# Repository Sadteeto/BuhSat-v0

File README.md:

BUH SAT so that we have an MVP for AURC! <br />
git clone this repo and import to platformIO. <br />
compiled uf2 file can be found in Actions tab - Artifacts <br />

capabilities: <br />
battery charging <br />
remote monitoring up to 40km <br />
temperature monitoring<br />
9-DOF motion monitoring <br />
 - gyro <br />
 - accel <br />
 - mag <br />

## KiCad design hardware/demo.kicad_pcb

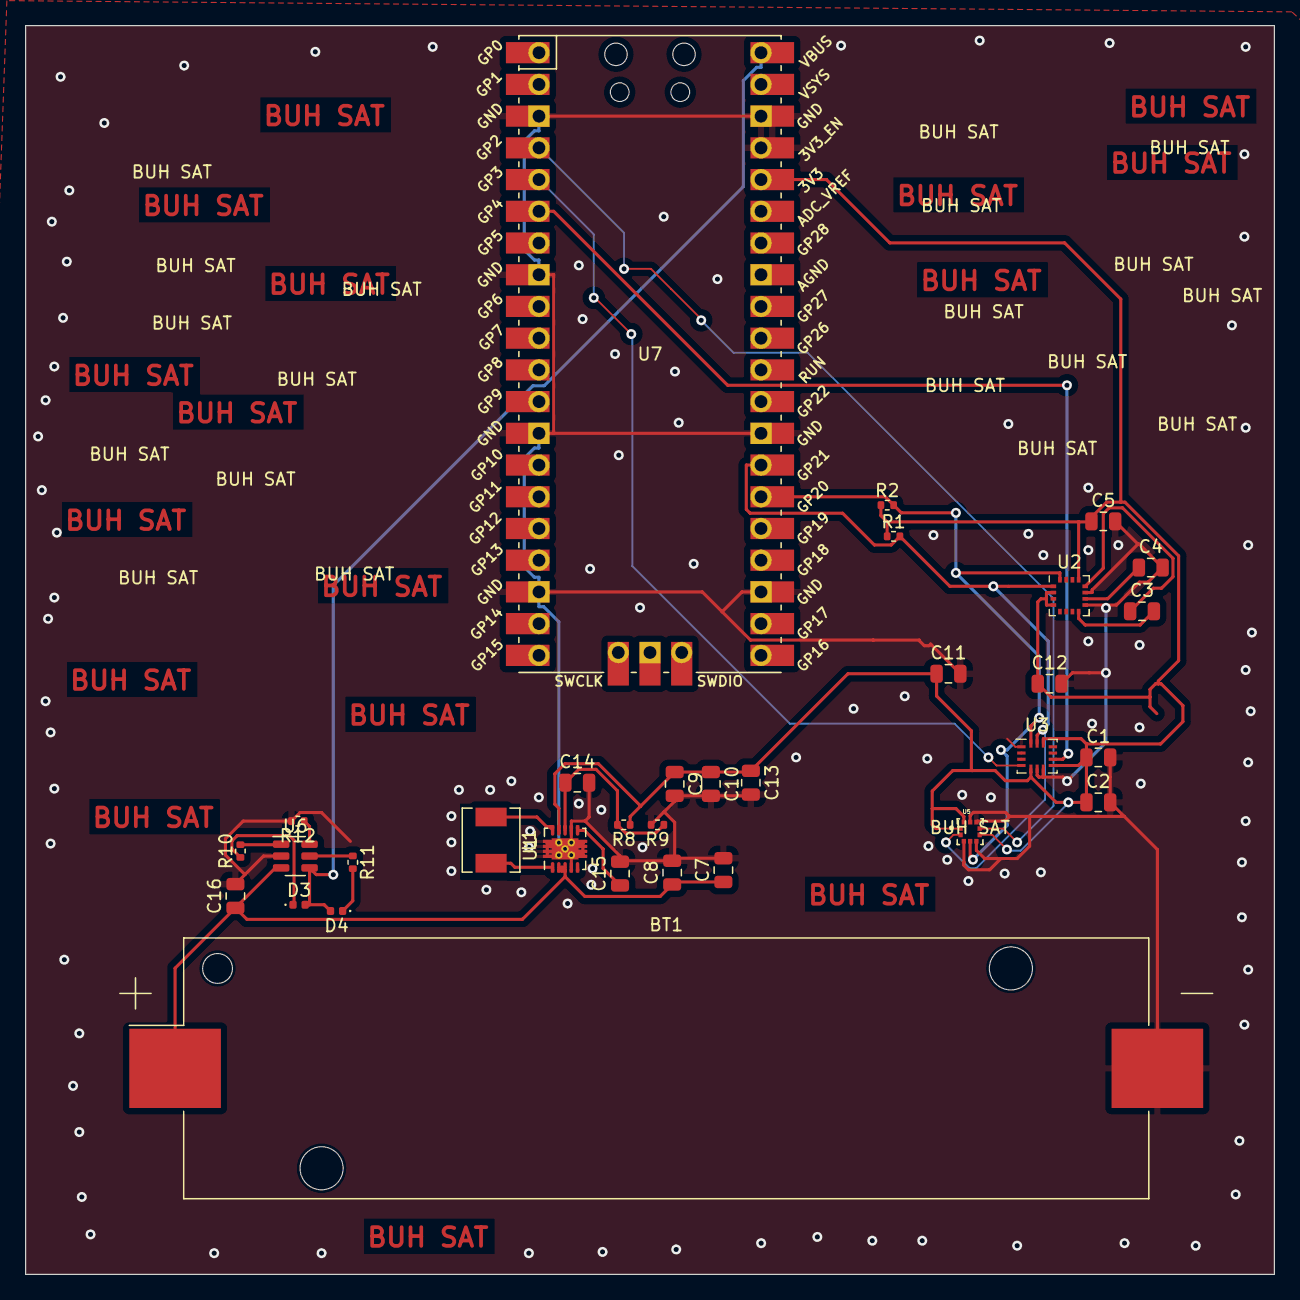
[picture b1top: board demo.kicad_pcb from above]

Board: 2 copper layers, 100.0 x 100.0 mm, 32 parts (0 on the bottom side), 21 nets.

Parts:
BT1: Battery; BatteryHolder_Keystone_1042_1x18650
C1, C2, C5, C11, C12, C15: 100nF; C_0805_2012Metric
C3: 220nF; C_0805_2012Metric
C4: 4.7 uF; C_0805_2012Metric
C7, C8, C16: 10uF; C_0805_2012Metric
C9, C10, C13: 22uF; C_0805_2012Metric
C14: 10pF; C_0805_2012Metric
D3: LED_Red; LED_0402_1005Metric
D4: LED_Green; LED_0402_1005Metric
L1: 1Uh; L_Chilisin_BMRA00040420
R1, R2: 4.7k; R_0402_1005Metric
R8: 560k; R_0402_1005Metric
R9: 100k; R_0402_1005Metric
R10, R11, R12: 10k; R_0402_1005Metric
U1: TPS63060; Texas_S-PWSON-N10_ThermalVias
U2: QMC5883L; LGA-16_3x3mm_P0.5mm
U3: BMI160; Bosch_LGA-14_3x2.5mm_P0.5mm
U5: BMP388; PQFN50P200X200X80-10N
U6: TP4057; SOT-23-6
U7: Pico; RPi_Pico_SMD_TH

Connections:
+3V3: C1.1, C2.1, C5.1, C9.1, C10.1, C11.1, C12.1, C13.1, R1.1, R2.1, R8.1, U1.9 (VOUT), U2.2 (VDD), U2.4 (S1), U2.13 (VDDIO), U3.5 (VDDIO), U3.8 (VDD), U3.12 (CSB), U5.1 (VDDIO), U5.6 (CSB), U5.10 (VDD), U7.36 (3V3)
GND: BT1.2 (-), C1.2, C2.2, C4.2, C5.2, C7.2, C8.2, C9.2, C10.2, C11.2, C12.2, C13.2, C14.2, C15.2, C16.2, R9.2, R12.2, U1.4 (PS/SYNC), U1.7 (GND), U1.11 (PGND), U2.9 (GND), U2.11 (GND), U3.1 (SDO), U3.6 (GNDIO), U3.7 (GND), U5.3 (VSS), U5.5 (SDO), U5.8 (VSS), U5.9 (VSS), U6.2 (GND), U7.3 (GND), U7.8 (GND), U7.13 (GND), U7.18 (GND), U7.23 (GND), U7.28 (GND), U7.37 (3V3_EN), U7.38 (GND)
INT: U5.7 (INT), U7.4 (GPIO2)
INT1: U3.4 (INT1), U7.5 (GPIO3)
INT2: U3.9 (INT2), U7.6 (GPIO4)
unnamed: D3.1 (K), R10.1
unnamed: D4.1 (K), R11.2
unnamed: C14.1, R8.2, R9.1, U1.8 (FB)
unnamed: L1.2, U1.1 (L1)
unnamed: L1.1, U1.10 (L2)
unnamed: C15.1, U1.6 (VAUX)
unnamed: C4.1, U2.10 (C1)
unnamed: C3.1, U2.12 (SETC)
unnamed: C3.2, U2.8 (STEP)
unnamed: R10.2, U6.1 (CHRG)
unnamed: R12.1, U6.6 (PROG)
unnamed: R11.1, U6.5 (STDBY)
SCL: R1.2, U2.1 (SCL), U3.13 (SCx), U5.2 (SCK), U7.27 (GPIO21)
SDA: R2.2, U2.16 (SDA), U3.14 (SDx), U5.4 (SDI), U7.26 (GPIO20)
V-USB: D3.2 (A), D4.2 (A), U6.4 (VCC), U7.40 (VBUS)
VBAT: BT1.1 (+), C7.1, C8.1, C16.1, U1.2 (VIN), U1.3 (EN), U6.3 (BATT)

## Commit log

2024-03-28 initial commit buh
2024-03-28 buhpdate
2024-03-28 BUHSENSE
2024-03-28 BUHPDATE2
2024-03-28 BUHPDATE3
2024-03-29 Buhg
2024-03-29 hardware added
2024-03-29 modified i2c address for bmp390L
2024-03-29 gitaction!
2024-03-29 update workflow
2024-05-12 Changed imu axis
2024-08-08 maybe works for esp32
2024-08-08 updated data struct with new data and pin conf for esp32
2024-09-19 removed pi build, hope action works
